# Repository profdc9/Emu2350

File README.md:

# EmuBoard2350

By Daniel L. Marks

This is an economical layout of a [FRANK](https://github.com/rh1tech/frank)-type multiemulator board,
intended to be manufactured by JLCPCB PCBA on a four layer board, using mostly basic parts.
It is both intended to be a fun gaming platform and a good educational project.
Extra pins of the RP2350B are exposed so that it may be usable for other projects, and there
are through-hole part components that are left unpopulated for learning soldering.

The major deviation from the FRANK design is that the NES pins are brought to a header rather
than a DE-9 male connector.  This was done because already-built famiclone-type controllers could
not be found.  Instead, the pins are brought to KF141V spring terminals, and a replacement
NES controller may have its connector removed and wires inserted into the terminals, or a
custom connector may be used.  A barrel jack is also provided so a standard wallwart that
one might have from another device may be used for power.

To support more than one USB device, an external USB hub needs to be plugged into the USB A
socket, for example when using a keyboard and a mouse.

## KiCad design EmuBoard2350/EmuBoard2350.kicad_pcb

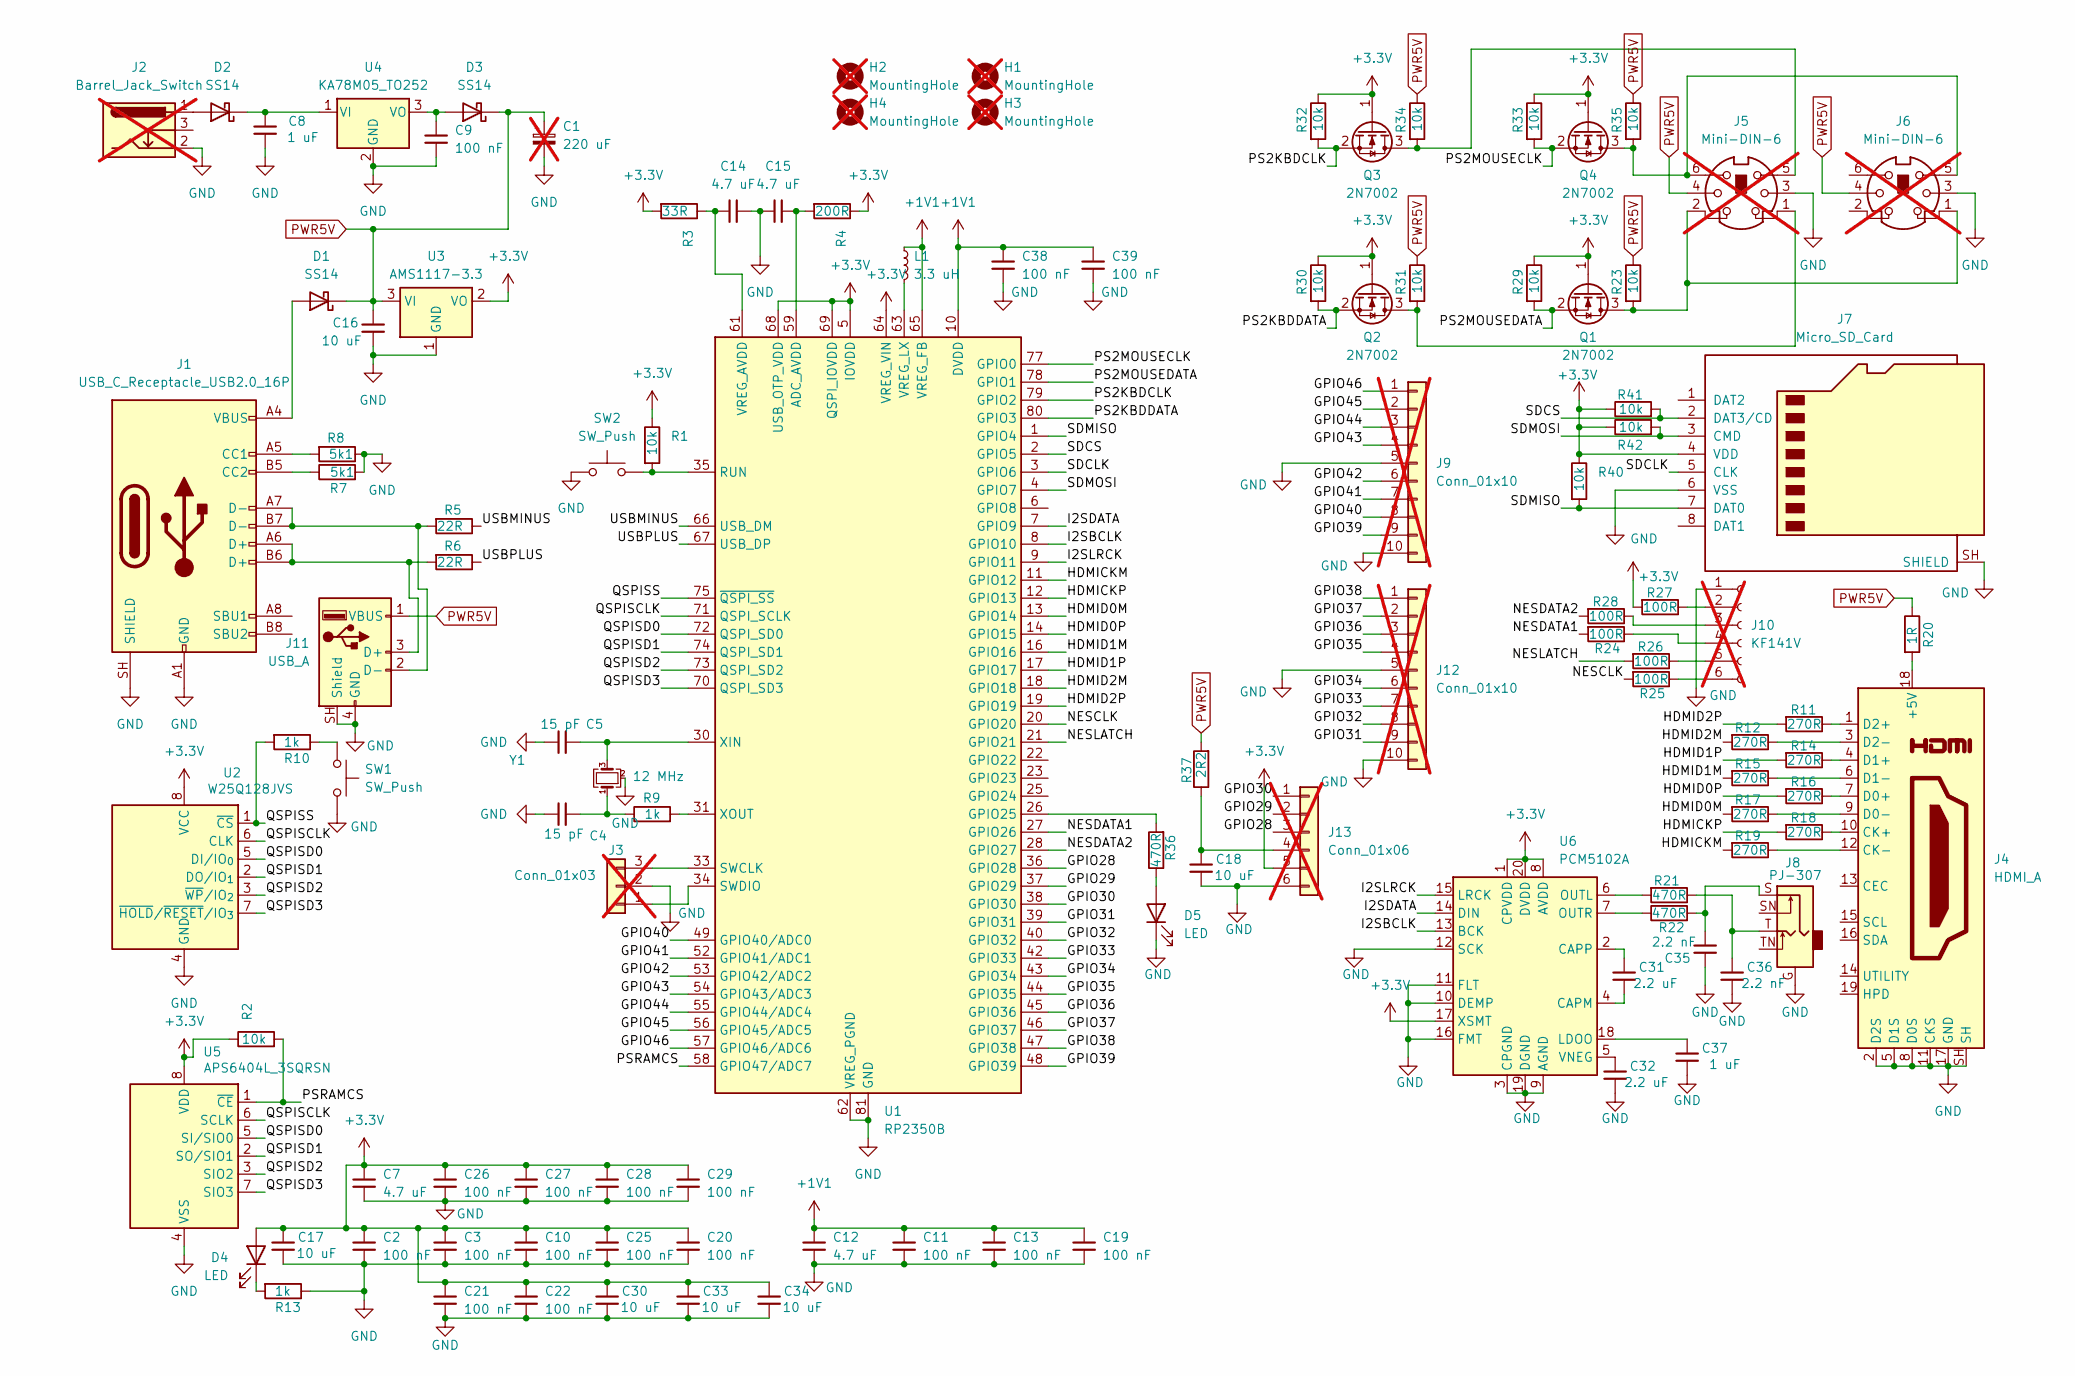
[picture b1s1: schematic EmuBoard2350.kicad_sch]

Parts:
C1: 220 uF; CP_Radial_D5.0mm_P2.00mm; LCSC DNP; not fitted
C2, C3, C9, C10, C11, C13, C19, C20, C21, C22, C25, C26, C27, C28, C29, C38, C39: 100 nF; C_0402_1005Metric; LCSC C1525
C4, C5: 15 pF; C_0402_1005Metric; LCSC C1548
C7, C12, C14, C15: 4.7 uF; C_0603_1608Metric; LCSC C19666
C8, C37: 1 uF; C_0603_1608Metric; LCSC C15849
C16, C17, C18, C30, C33, C34: 10 uF; C_0603_1608Metric; LCSC C19702
C31, C32: 2.2 uF; C_0603_1608Metric; LCSC C23630
C35, C36: 2.2 nF; C_0603_1608Metric; LCSC C1604
D1, D2, D3: SS14; D_SMA; LCSC C2480
D4: LED; LED_0805_2012Metric; LCSC C2297
D5: LED; LED_0805_2012Metric; LCSC C2296
H1, H2, H3, H4: MountingHole; MountingHole_3.2mm_M3; not fitted
J1: USB_C_Receptacle_USB2.0_16P; TYPE-C-31-M-12; LCSC C165948
J2: Barrel_Jack_Switch; BarrelJack_Horizontal; not fitted
J3: Conn_01x03; PinHeader_1x03_P2.54mm_Vertical; not fitted
J4: HDMI_A; HDMI_A_Molex_208658-1001_Horizontal; LCSC C111617
J5, J6: Mini-DIN-6; Connector_Mini-DIN_Female_6Pin_2rows; not fitted
J7: Micro_SD_Card; GCT-MEM2055-00-190-01-A; LCSC C91145
J8: PJ-307; LCSC C16684
J9, J12: Conn_01x10; KF141-terminal-block-10pos; not fitted
J10: KF141V; KF141-terminal-block-6pos; not fitted
J11: USB_A; USB_A_Connfly_DS1095; LCSC C2344
J13: Conn_01x06; KF141-terminal-block-6pos; not fitted
L1: 3.3 uH; L_1008_2520Metric; LCSC C5832359
Q1, Q2, Q3, Q4: 2N7002; SOT-23; LCSC C8545
R1, R2, R23, R29, R30, R31, R32, R33, R34, R35, R40, R41, R42: 10k; R_0402_1005Metric; LCSC C25744
R3: 33R; R_0402_1005Metric; LCSC C25105
R4: 200R; R_0402_1005Metric; LCSC C25087
R5, R6: 22R; R_0402_1005Metric; LCSC C25092
R7, R8: 5k1; R_0402_1005Metric; LCSC C25905
R9, R10, R13: 1k; R_0402_1005Metric; LCSC C11702
R11, R12, R14, R15, R16, R17, R18, R19: 270R; R_0603_1608Metric; LCSC C22966
R20: 1R; R_0805_2012Metric; LCSC C25271
R21, R22, R36: 470R; R_0805_2012Metric; LCSC C17710
R24, R25, R26, R27, R28: 100R; R_0603_1608Metric; LCSC C22775
R37: 2R2; R_0805_2012Metric; LCSC C17521
SW1, SW2: SW_Push; TS-1088-AR02016; LCSC C720477
U1: RP2350B; QFN-80-1EP_10x10mm_P0.4mm_EP3.4x3.4mm
U2: W25Q128JVS; SOIC-8_5.3x5.3mm_P1.27mm; LCSC C97521
U3: AMS1117-3.3; SOT-223-3_TabPin2; LCSC C6186
U4: KA78M05_TO252; TO-252-2; LCSC C58069
U5: APS6404L_3SQRSN; SOIC-8_3.9x4.9mm_P1.27mm; LCSC C5333729
U6: PCM5102A; TSSOP-20_4.4x6.5mm_P0.65mm; LCSC C107671
Y1: 12 MHz; Crystal_SMD_3225-4Pin_3.2x2.5mm; LCSC C20625731

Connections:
+1V1: C11.1, C12.1, C13.1, C19.1, C38.1, C39.1, L1.1, U1.10 (DVDD), U1.32 (DVDD), U1.51 (DVDD), U1.65 (VREG_FB)
+3.3V: C2.1, C3.1, C7.1, C10.1, C17.1, C20.1, C21.1, C22.1, C25.1, C26.1, C27.1, C28.1, C29.1, C30.1, C33.1, C34.1, D4.2 (A), J7.4 (VDD), J13.5, Q1.1 (G), Q2.1 (G), Q3.1 (G), Q4.1 (G), R1.1, R2.1, R3.2, R4.1, R27.2, R29.1, R30.1, R32.1, R33.1, R40.1, R41.1, R42.1, U1.5 (IOVDD), U1.15 (IOVDD), U1.24 (IOVDD), U1.29 (IOVDD), U1.41 (IOVDD), U1.50 (IOVDD), U1.60 (IOVDD), U1.64 (VREG_VIN), U1.68 (USB_OTP_VDD), U1.69 (QSPI_IOVDD), U1.76 (IOVDD), U2.8 (VCC), U3.2 (VO), U5.8 (VDD), U6.1 (CPVDD), U6.8 (AVDD), U6.17 (XSMT), U6.20 (DVDD)
/GPIO28: J13.3, U1.36 (GPIO28)
/GPIO29: J13.2, U1.37 (GPIO29)
/GPIO30: J13.1, U1.38 (GPIO30)
/GPIO31: J12.9, U1.39 (GPIO31)
/GPIO32: J12.8, U1.40 (GPIO32)
/GPIO33: J12.7, U1.42 (GPIO33)
/GPIO34: J12.6, U1.43 (GPIO34)
/GPIO35: J12.4, U1.44 (GPIO35)
/GPIO36: J12.3, U1.45 (GPIO36)
/GPIO37: J12.2, U1.46 (GPIO37)
/GPIO38: J12.1, U1.47 (GPIO38)
/GPIO39: J9.9, U1.48 (GPIO39)
/GPIO40: J9.8, U1.49 (GPIO40/ADC0)
/GPIO41: J9.7, U1.52 (GPIO41/ADC1)
/GPIO42: J9.6, U1.53 (GPIO42/ADC2)
/GPIO43: J9.4, U1.54 (GPIO43/ADC3)
/GPIO44: J9.3, U1.55 (GPIO44/ADC4)
/GPIO45: J9.2, U1.56 (GPIO45/ADC5)
/GPIO46: J9.1, U1.57 (GPIO46/ADC6)
/HDMICKM: R19.2, U1.11 (GPIO12)
/HDMICKP: R18.2, U1.12 (GPIO13)
/HDMID0M: R17.2, U1.13 (GPIO14)
/HDMID0P: R16.2, U1.14 (GPIO15)
/HDMID1M: R15.2, U1.16 (GPIO16)
/HDMID1P: R14.2, U1.17 (GPIO17)
/HDMID2M: R12.2, U1.18 (GPIO18)
/HDMID2P: R11.2, U1.19 (GPIO19)
/I2SBCLK: U1.8 (GPIO10), U6.13 (BCK)
/I2SDATA: U1.7 (GPIO9), U6.14 (DIN)
/I2SLRCK: U1.9 (GPIO11), U6.15 (LRCK)
/NESCLK: R25.2, U1.20 (GPIO20)
/NESDATA1: R24.2, U1.27 (GPIO26)
/NESDATA2: R28.2, U1.28 (GPIO27)
/NESLATCH: R26.2, U1.21 (GPIO21)
/PS2KBDCLK: Q3.2 (S), R32.2, U1.79 (GPIO2)
/PS2KBDDATA: Q2.2 (S), R30.2, U1.80 (GPIO3)
/PS2MOUSECLK: Q4.2 (S), R33.2, U1.77 (GPIO0)
/PS2MOUSEDATA: Q1.2 (S), R29.2, U1.78 (GPIO1)
/PSRAMCS: R2.2, U1.58 (GPIO47/ADC7), U5.1 (~CE)
/QSPISCLK: U1.71 (QSPI_SCLK), U2.6 (CLK), U5.6 (SCLK)
/QSPISD0: U1.72 (QSPI_SD0), U2.5 (DI/IO_{0}), U5.5 (SI/SIO0)
/QSPISD1: U1.74 (QSPI_SD1), U2.2 (DO/IO_{1}), U5.2 (SO/SIO1)
/QSPISD2: U1.73 (QSPI_SD2), U2.3 (~WP/IO_{2}), U5.3 (SIO2)
/QSPISD3: U1.70 (QSPI_SD3), U2.7 (~HOLD/~RESET/IO_{3}), U5.7 (SIO3)
/QSPISS: R10.2, U1.75 (~QSPI_SS), U2.1 (~CS)
/SDCLK: J7.5 (CLK), U1.3 (GPIO6)
/SDCS: J7.2 (DAT3/CD), R41.2, U1.2 (GPIO5)
/SDMISO: J7.7 (DAT0), R40.2, U1.1 (GPIO4)
/SDMOSI: J7.3 (CMD), R42.2, U1.4 (GPIO7)
/USBMINUS: R5.1, U1.66 (USB_DM)
/USBPLUS: R6.1, U1.67 (USB_DP)
GND: C1.2, C2.2, C3.2, C4.2, C5.2, C7.2, C8.2, C9.2, C10.2, C11.2, C12.2, C13.2, C14.2, C15.1, C16.2, C17.2, C18.2, C19.2, C20.2, C21.2, C22.2, C25.2, C26.2, C27.2, C28.2, C29.2, C30.2, C32.2, C33.2, C34.2, C35.1, C36.2, C37.2, C38.2, C39.2, D5.1 (K), J1.A1 (GND), J1.A12 (GND), J1.B1 (GND), J1.B12 (GND), J1.SH (SHIELD), J2.2, J3.2, J4.2 (D2S), J4.5 (D1S), J4.8 (D0S), J4.11 (CKS), J4.17 (GND), J4.SH, J5.3, J6.3, J7.6 (VSS), J7.SH (SHIELD), J8.G, J9.5, J9.10, J10.1, J11.4 (GND), J11.SH (Shield), J12.5, J12.10, J13.6, R7.2, R8.1, R13.1, SW1.2, SW2.1, U1.62 (VREG_PGND), U1.81 (GND), U2.4 (GND), U3.1 (GND), U4.2 (GND), U5.4 (VSS), U6.3 (CPGND), U6.9 (AGND), U6.10 (DEMP), U6.11 (FLT), U6.12 (SCK), U6.16 (FMT), U6.19 (DGND), Y1.2 (G), Y1.4 (G)
unnamed: C4.1, R9.1, Y1.1
unnamed: C35.2, J8.S, R22.2
unnamed: C36.1, J8.T, R21.1
unnamed: D1.2 (A), J1.A4 (VBUS), J1.A9 (VBUS), J1.B4 (VBUS), J1.B9 (VBUS)
unnamed: D2.2 (A), J2.1
unnamed: C8.1, D2.1 (K), U4.1 (VI)
unnamed: C9.1, D3.2 (A), U4.3 (VO)
unnamed: D4.1 (K), R13.2
unnamed: D5.2 (A), R36.1
unnamed: J1.A5 (CC1), R8.2
unnamed: J1.B5 (CC2), R7.1
unnamed: J3.1, U1.34 (SWDIO)
unnamed: J3.3, U1.33 (SWCLK)
unnamed: J4.18 (+5V), R20.2
unnamed: J4.10 (CK+), R18.1
unnamed: J4.12 (CK-), R19.1
unnamed: J4.7 (D0+), R16.1
unnamed: J4.9 (D0-), R17.1
unnamed: J4.4 (D1+), R14.1
unnamed: J4.6 (D1-), R15.1
unnamed: J4.1 (D2+), R11.1
unnamed: J4.3 (D2-), R12.1
unnamed: J10.2, R27.1
unnamed: J10.3, R28.1
unnamed: J10.4, R24.1
unnamed: J10.5, R26.1
unnamed: J10.6, R25.1
unnamed: J1.A6 (D+), J1.B6 (D+), J11.3 (D+), R6.2
unnamed: J1.A7 (D-), J1.B7 (D-), J11.2 (D-), R5.2
unnamed: C18.1, J13.4, R37.1
unnamed: J5.2, J6.1, Q1.3 (D), R23.2
unnamed: J5.1, Q2.3 (D), R31.2
unnamed: J5.5, Q3.3 (D), R34.2
unnamed: J5.6, J6.5, Q4.3 (D), R35.2
unnamed: R10.1, SW1.1
unnamed: C15.2, R4.2, U1.59 (ADC_AVDD)
unnamed: R36.2, U1.26 (GPIO25)
unnamed: R1.2, SW2.2, U1.35 (RUN)
unnamed: C14.1, R3.1, U1.61 (VREG_AVDD)
unnamed: L1.2, U1.63 (VREG_LX)
unnamed: C5.1, U1.30 (XIN), Y1.3
unnamed: R9.2, U1.31 (XOUT)
unnamed: C31.2, U6.4 (CAPM)
unnamed: C31.1, U6.2 (CAPP)
unnamed: C37.1, U6.18 (LDOO)
unnamed: R21.2, U6.6 (OUTL)
unnamed: R22.1, U6.7 (OUTR)
unnamed: C32.1, U6.5 (VNEG)
PWR5V: C1.1, C16.1, D1.1 (K), D3.1 (K), J5.4, J6.4, J11.1 (VBUS), R20.1, R23.1, R31.1, R34.1, R35.1, R37.2, U3.3 (VI)

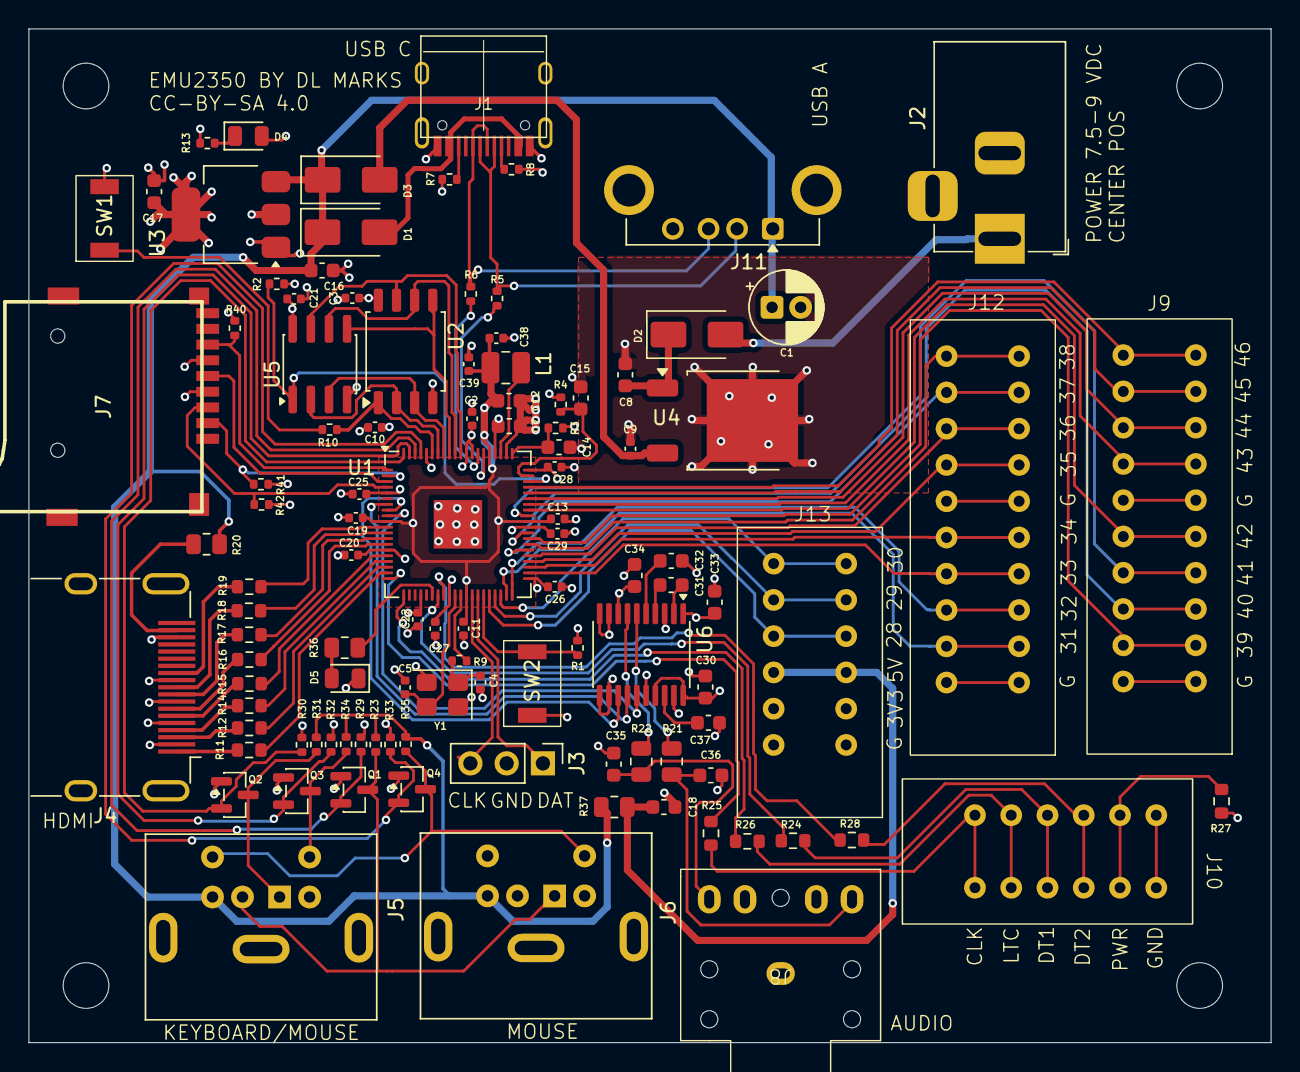
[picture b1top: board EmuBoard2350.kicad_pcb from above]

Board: 4 copper layers, 87.0 x 71.0 mm, 112 parts (0 on the bottom side), 103 nets.

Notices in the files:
EmuBoard2350/EmuBoard2350.kicad_pcb:
CC-BY-SA 4.0
